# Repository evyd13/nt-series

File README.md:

# nt-series

## FC660C
Please see the controller for the FC660C [here](https://github.com/evyd13/fc660c-controller).

## About
Replacement PCBs for the FC660m, FC750r, FC980m and FC210TP.

Each of these PCBs have been tested by me, but I cannot guarantee that they work for you.

Use the latest nightly version of KiCAD to open these files. Gerbers and BOM are included for every PCB.

## Stabilizers
All of these PCB designs support PCB mounted stabilizers, but only with a custom made plate, as the stock plate tabs prevent you from putting the plate and PCB together with PCB mounted stabilizers installed.

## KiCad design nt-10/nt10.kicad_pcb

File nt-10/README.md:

# nt-10 daughterboard for Leopold keyboards

The nt-10 is a USB-C daughterboard designed to fit the Leopold range of keyboards.  
At the time of writing those are the:

- FC750r
- FC980m
- FC900r

## Installation

Upon removal of the old (probably Mini USB) daughterboard, carefully insert the nt-10 and make sure the USB-C connector fits the cutout in the case. If it does not fit, you can use a small file to increase the cutout size.

### Wiring

The wiring is as follows:

You might have to swap the wires on some boards, I had to on the 980m. Lift up the tabs using tweezers or a small knife (don't hurt yourself!) and take out the wires, then press the tabs back down and insert the wires in the correct order.

## BOM

| LCSC part # | Description   | Value | Package  | Amount |
| ----------- | ------------- | ----- | -------- | ------:|
| C27834      | Resistor      | 5.1k  | 0805     | 2      |
| C261942     | Fuse          |       | 0805     | 1      |
| C7519       | ESD prot.     |       | SOT32-6  | 1      |
| C165948     | USB-C conn.   |       |          | 1      |
| C160404     | JST SH 1x4    |       |          | 1      |
| C392176     | PicoBlade 1x5 |       |          | 1      |

Use at your own risk.

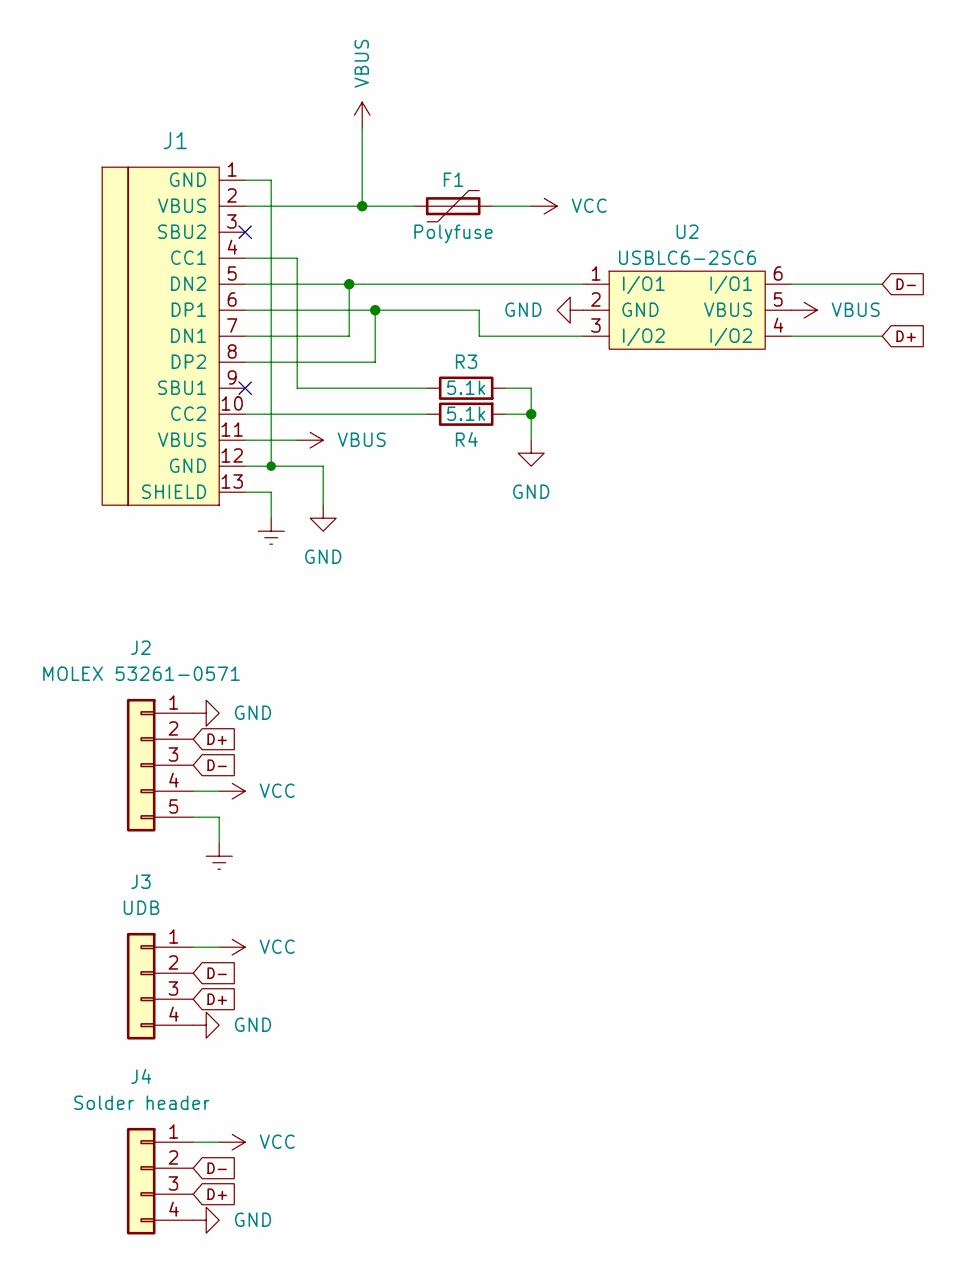
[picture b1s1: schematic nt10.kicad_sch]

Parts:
F1: Polyfuse; F_0805; LCSC Part C261942
J1: HRO-TYPE-C-31-M-12; LCSC Part C165948
J2: MOLEX 53261-0571; Molex_PicoBlade_53261-0571_1x05-1MP_P1.25mm_Horizontal; LCSC Part C392176
J3: UDB; CONN_JST_SH_SM04B-SRSS-TB_1x04-1MP_P1.00mm_Horizontal; LCSC Part C160404
J4: Solder header; 01x04-solder-header
R3, R4: 5.1k; R_0805; LCSC Part C27834
U2: USBLC6-2SC6; LCSC Part C7519

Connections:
D+: J2.2, J3.3, J4.3, U2.4 (I/O2)
D-: J2.3, J3.2, J4.2, U2.6 (I/O1)
Earth: J1.13 (SHIELD), J2.5
GND: J1.1 (GND), J1.12 (GND), J2.1, J3.4, J4.4, R3.2, R4.2, U2.2 (GND)
unnamed: J1.4 (CC1), R3.1
unnamed: J1.5 (DN2), J1.7 (DN1), U2.1 (I/O1)
unnamed: J1.6 (DP1), J1.8 (DP2), U2.3 (I/O2)
unnamed: J1.10 (CC2), R4.1
VBUS: F1.1, J1.2 (VBUS), J1.11 (VBUS), U2.5 (VBUS)
VCC: F1.2, J2.4, J3.1, J4.1

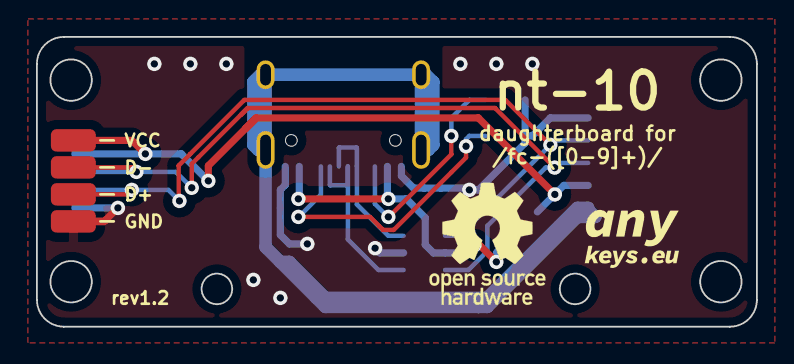
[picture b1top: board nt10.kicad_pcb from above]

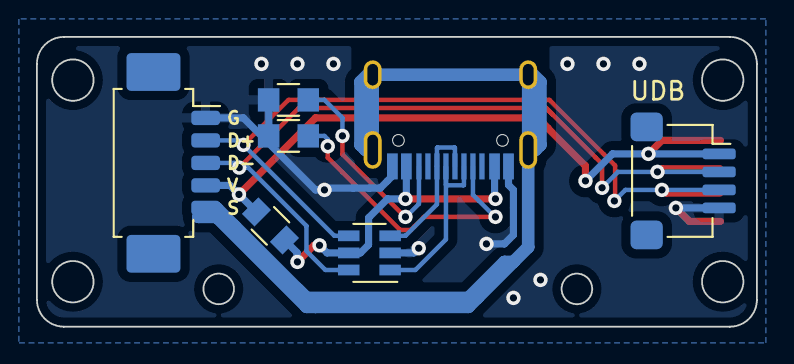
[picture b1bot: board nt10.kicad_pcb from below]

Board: 2 copper layers, 40.0 x 16.1 mm, 8 parts (7 on the bottom side), 10 nets.

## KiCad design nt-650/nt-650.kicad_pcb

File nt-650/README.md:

# nt-650

This is a replacement controller PCB for the FC650M.

## Revisions

### rev1
First revision

## BOM

| LCSC part # | Description   | Value | Package  | Amount |
| ----------- | ------------- | ----- | -------- | ------:|
| C14663      | Capacitor     | 0.1uF | 0603     | 4      |
| C19666      | Capacitor     | 4.7uF | 0603     | 1      |
| C15849      | Capacitor     | 1uF   | 0603     | 1      |
| C261942     | Fuse          |       | 0805     | 1      |
| C124360     | Pin header    | 2x16  | TH       | 1      |
| C25804      | Resistor      | 10K   | 0603     | 2      |
| C112161     | MCU           | 32U4  | QFN-44   | 1      |
| C341521     | Resonator     | 16MHz | SMD      | 1      |
| C92584      | Switch        |       | SMD      | 1      |

Use at your own risk.

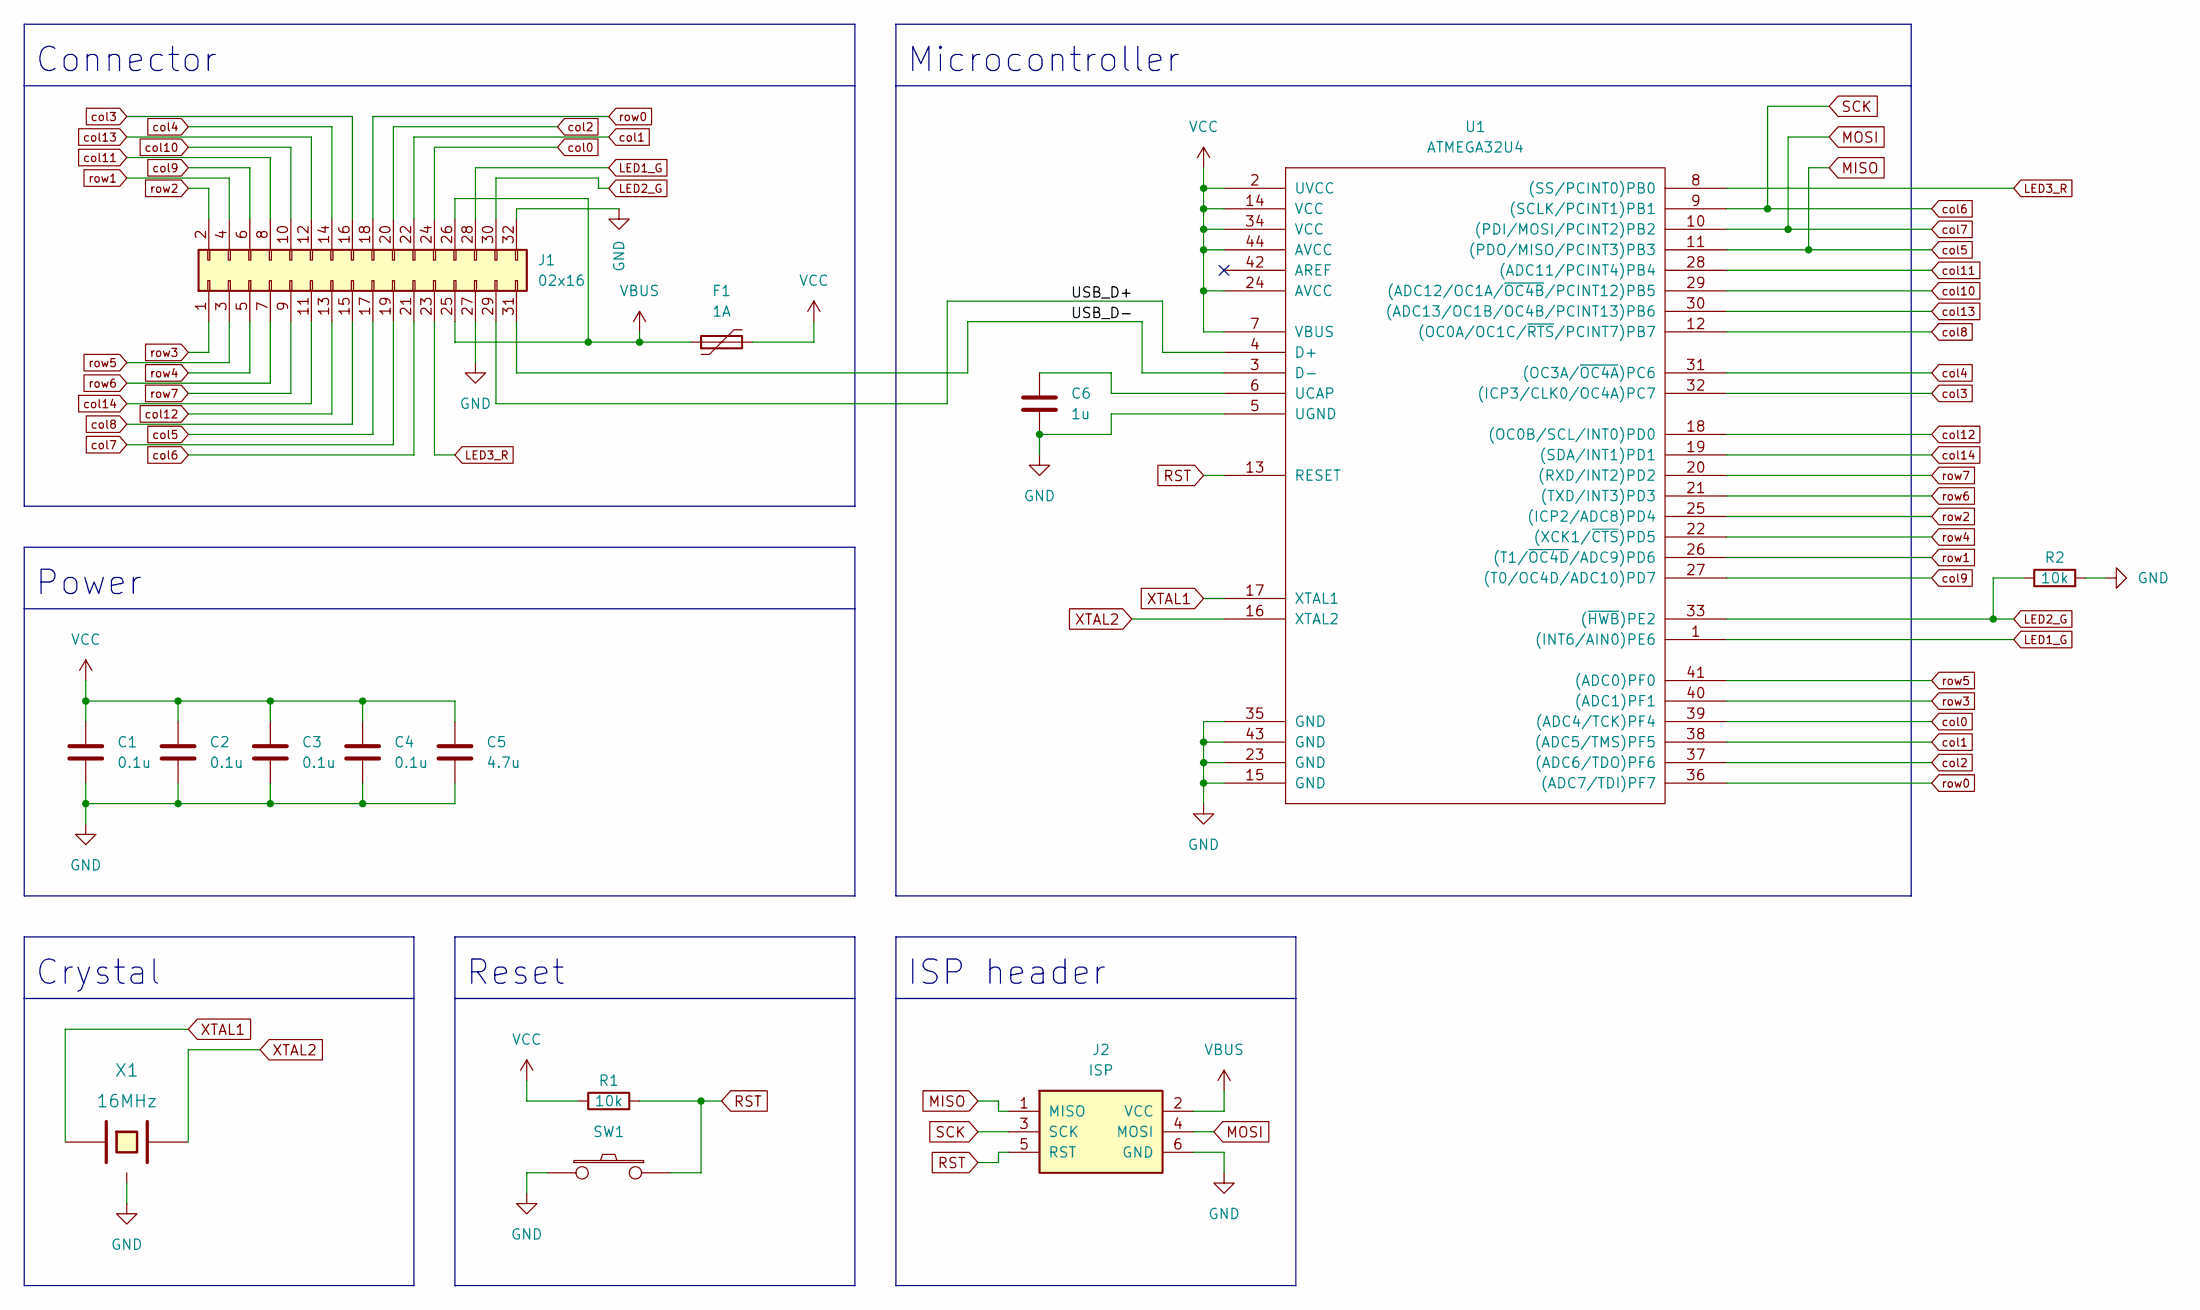
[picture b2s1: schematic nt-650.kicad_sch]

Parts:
C1, C2, C3, C4: 0.1u; C_0603; Part number CC0603KRX7R9BB104; LCSC Part C14663
C5: 4.7u; C_0603; Part number CL10A475KO8NNNC; LCSC Part C19666
C6: 1u; C_0603; Part number CL10A105KB8NNNC; LCSC Part C15849
F1: 1A; R_0805; Part number TLC-PSMD050; LCSC Part C261942
J1: 02x16; PinHeader_2x16_P2.00mm_Vertical; JLCPCB BOM 0
J2: ISP; CONN_isp_standard; JLCPCB BOM 0
R1, R2: 10k; R_0603; Part number 0603WAF1002T5E; LCSC Part C25804
SW1: SW_PUSH; SWITCH_SPST_TL3342_W_JUMP; Part number TS-1187A-B-A-B; LCSC Part C318884
U1: ATMEGA32U4; MCU_ATMEGA32U4-MU; Part number ATMEGA32U4-MU; LCSC Part C112161
X1: 16MHz; XTAL_SMD_Murata_CSTxExxV-3Pin_3.0x1.1mm; Part number CSTNE16M0V530000R0; LCSC Part C341521

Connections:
/USB_D+: J1.29, U1.4 (D+)
/USB_D-: J1.31, U1.3 (D-)
GND: C1.2, C2.2, C3.2, C4.2, C5.2, C6.2, J1.27, J1.32, J2.6 (GND), R2.2, SW1.1, U1.5 (UGND), U1.15 (GND), U1.23 (GND), U1.35 (GND), U1.43 (GND), X1.3
LED1_G: J1.28, U1.1 ((INT6/AIN0)PE6)
LED2_G: J1.30, R2.1, U1.33 ((~HWB)PE2)
LED3_R: J1.23, U1.8 ((SS/PCINT0)PB0)
MISO: J1.17, J2.1 (MISO), U1.11 ((PDO/MISO/PCINT3)PB3)
MOSI: J1.19, J2.4 (MOSI), U1.10 ((PDI/MOSI/PCINT2)PB2)
unnamed: C6.1, U1.6 (UCAP)
RST: J2.5 (RST), R1.2, SW1.2, U1.13 (RESET)
SCK: J1.21, J2.3 (SCK), U1.9 ((SCLK/PCINT1)PB1)
VBUS: F1.1, J1.25, J1.26, J2.2 (VCC)
VCC: C1.1, C2.1, C3.1, C4.1, C5.1, F1.2, R1.1, U1.2 (UVCC), U1.7 (VBUS), U1.14 (VCC), U1.24 (AVCC), U1.34 (VCC), U1.44 (AVCC)
XTAL1: U1.17 (XTAL1), X1.1
XTAL2: U1.16 (XTAL2), X1.2
col0: J1.24, U1.39 ((ADC4/TCK)PF4)
col1: J1.22, U1.38 ((ADC5/TMS)PF5)
col2: J1.20, U1.37 ((ADC6/TDO)PF6)
col3: J1.16, U1.32 ((ICP3/CLK0/OC4A)PC7)
col4: J1.14, U1.31 ((OC3A/~OC4A)PC6)
col8: J1.15, U1.12 ((OC0A/OC1C/~RTS/PCINT7)PB7)
col9: J1.6, U1.27 ((T0/OC4D/ADC10)PD7)
col10: J1.10, U1.29 ((ADC12/OC1A/~OC4B/PCINT12)PB5)
col11: J1.8, U1.28 ((ADC11/PCINT4)PB4)
col12: J1.13, U1.18 ((OC0B/SCL/INT0)PD0)
col13: J1.12, U1.30 ((ADC13/OC1B/OC4B/PCINT13)PB6)
col14: J1.11, U1.19 ((SDA/INT1)PD1)
row0: J1.18, U1.36 ((ADC7/TDI)PF7)
row1: J1.4, U1.26 ((T1/~OC4D/ADC9)PD6)
row2: J1.2, U1.25 ((ICP2/ADC8)PD4)
row3: J1.1, U1.40 ((ADC1)PF1)
row4: J1.5, U1.22 ((XCK1/~CTS)PD5)
row5: J1.3, U1.41 ((ADC0)PF0)
row6: J1.7, U1.21 ((TXD/INT3)PD3)
row7: J1.9, U1.20 ((RXD/INT2)PD2)

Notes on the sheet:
Microcontroller
Power
Reset
ISP header
Crystal
Connector

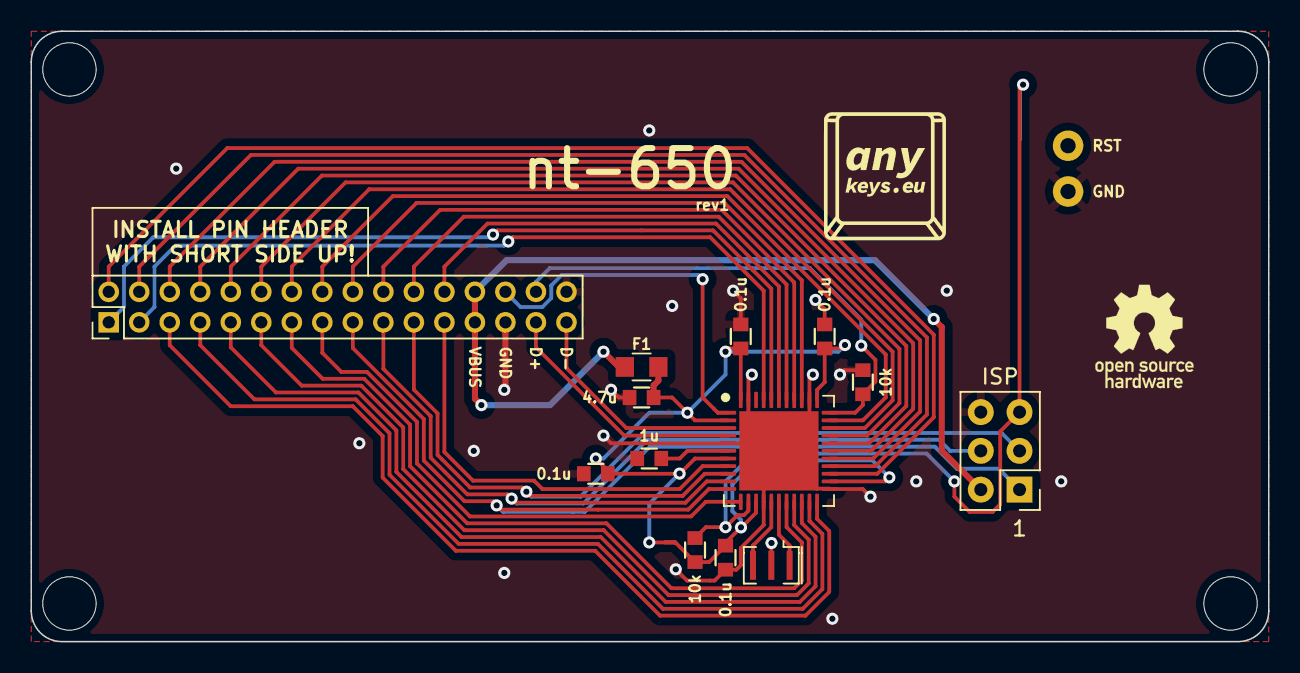
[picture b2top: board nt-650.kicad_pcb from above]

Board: 2 copper layers, 81.1 x 40.0 mm, 14 parts (1 on the bottom side), 35 nets.

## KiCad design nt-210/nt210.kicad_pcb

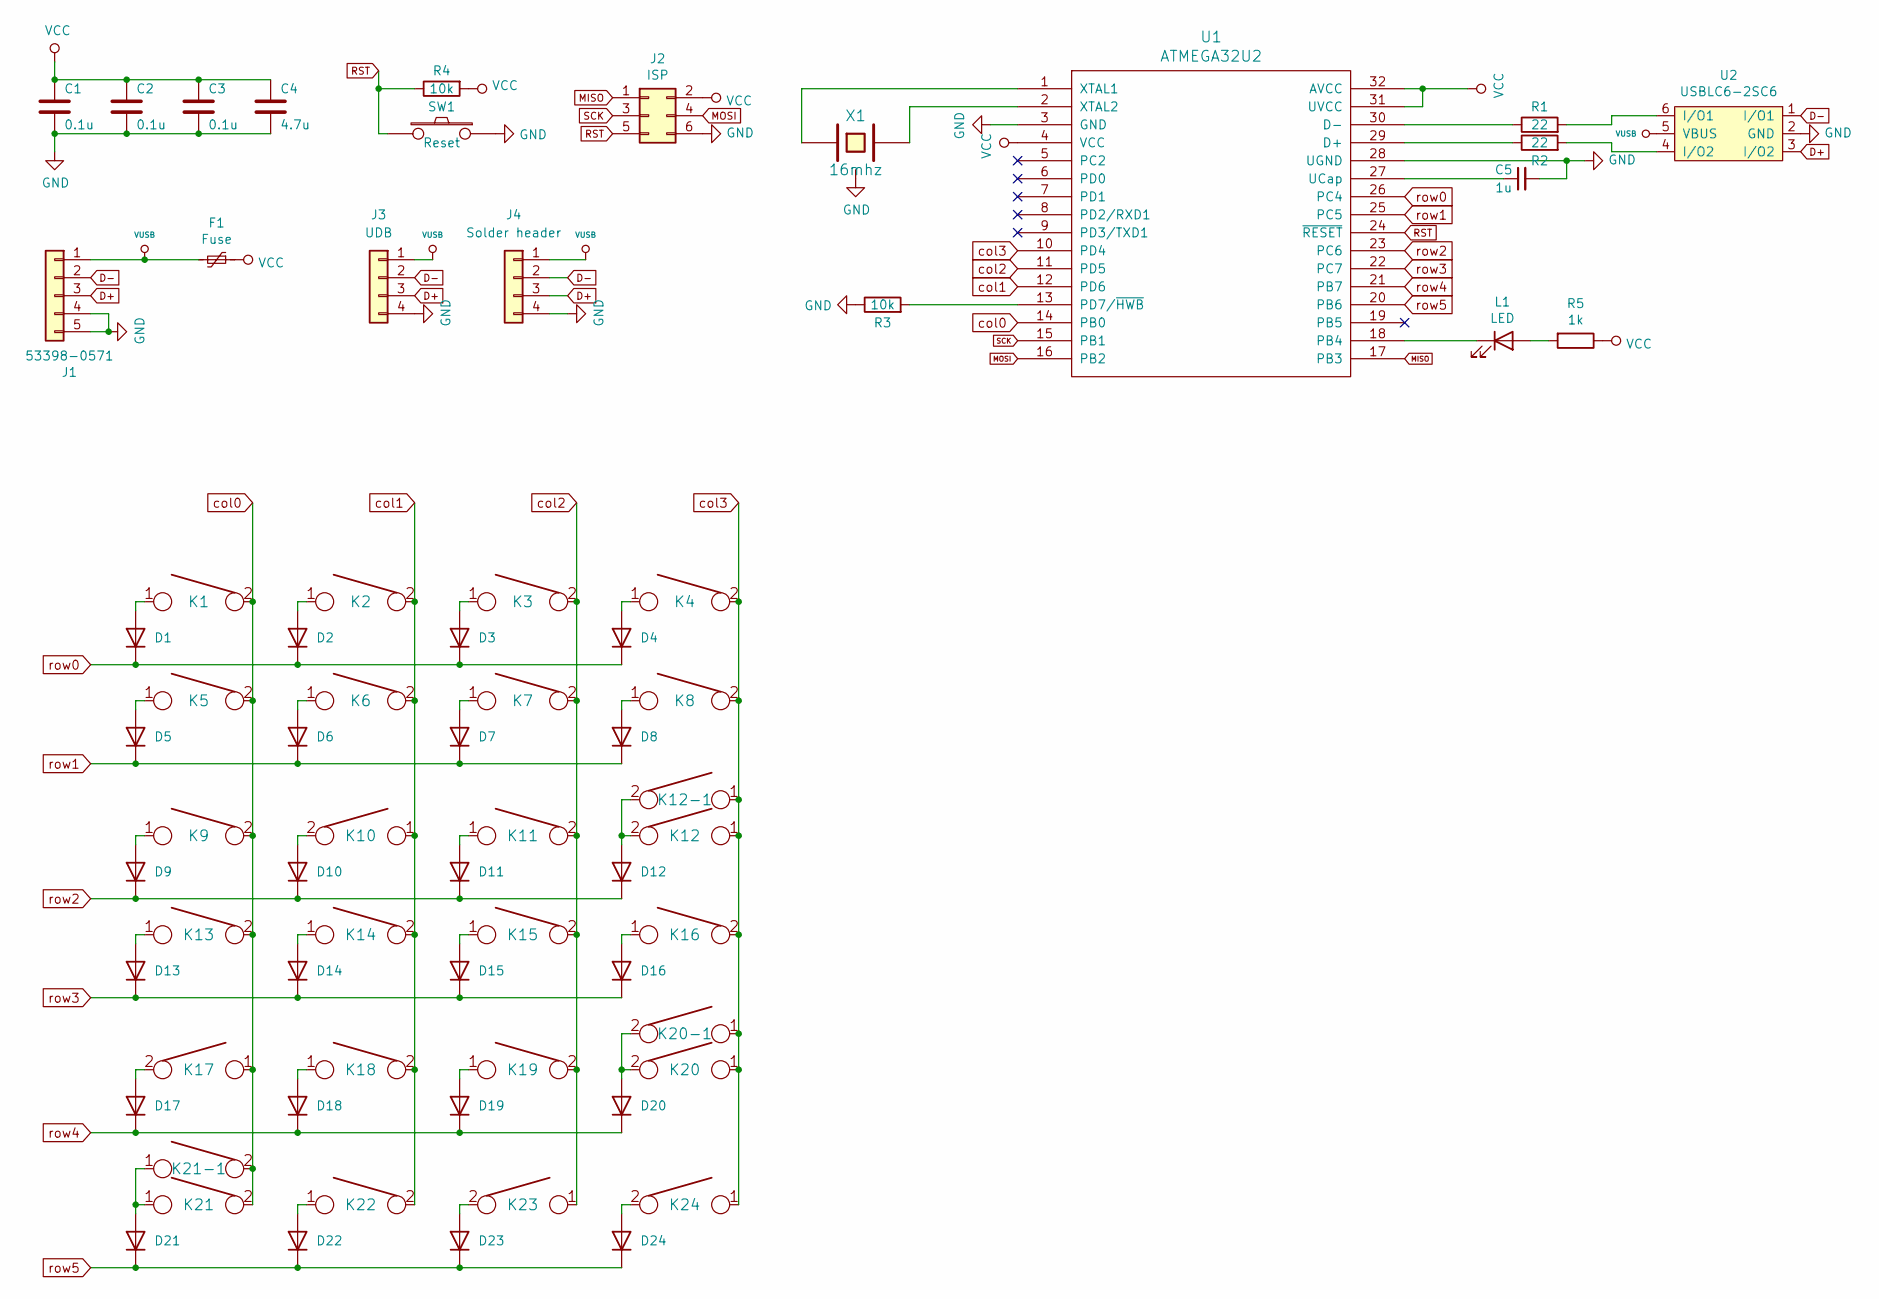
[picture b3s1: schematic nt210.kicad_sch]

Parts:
C1, C2, C3: 0.1u; C_0603
C4: 4.7u; C_0603
C5: 1u; C_0603
D1, D2, D3, D4, D5, D6, D7, D8, D9, D10, D11, D12, D13, D14, D15, D16, D17, D18, D19, D20, D21, D22, D23, D24: D; D_0805
F1: Fuse; F_0805
J1: 53398-0571; Molex-PicoBlade-533980571
J2: ISP; isp_standard
J3: UDB; JST_SH_SM04B-SRSS-TB_1x04-1MP_P1.00mm_Horizontal
J4: Solder header; solder_header
K1, K2, K3, K4, K5, K6, K7, K8, K9, K10, K11, K12-1, K13, K14, K15, K16, K17, K18, K19, K20-1, K21-1, K22, K23, K24: KEYSW; CHERRY_PLATE_100H
K12, K20: KEYSW; CHERRY_PLATE_200H_V
K21: KEYSW; CHERRY_PLATE_200H
L1: LED; CHERRY_MX_LED_neo
R1, R2: 22; R_0603
R3, R4: 10k; R_0603
R5: 1k; R_0603
SW1: Reset; SW_SPST_TL3342
U1: ATMEGA32U2
U2: USBLC6-2SC6
X1: 16mhz; Resonator_SMD_muRata_CSTNExxV-3Pin-p1.2

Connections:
D+: J1.3, J3.3, J4.3, U2.3 (I/O2)
D-: J1.2, J3.2, J4.2, U2.1 (I/O1)
GND: C1.2, C2.2, C3.2, C4.2, C5.2, J1.4, J1.5, J2.6, J3.4, J4.4, R3.1, SW1.1, U1.3 (GND), U1.28 (UGND), U2.2 (GND), X1.3
MISO: J2.1, U1.17 (PB3)
MOSI: J2.4, U1.16 (PB2)
unnamed: C5.1, U1.27 (UCap)
unnamed: D1.2 (A), K1.1
unnamed: D2.2 (A), K2.1
unnamed: D3.2 (A), K3.1
unnamed: D4.2 (A), K4.1
unnamed: D5.2 (A), K5.1
unnamed: D6.2 (A), K6.1
unnamed: D7.2 (A), K7.1
unnamed: D8.2 (A), K8.1
unnamed: D9.2 (A), K9.1
unnamed: D10.2 (A), K10.2
unnamed: D11.2 (A), K11.1
unnamed: D12.2 (A), K12.2, K12-1.2
unnamed: D13.2 (A), K13.1
unnamed: D14.2 (A), K14.1
unnamed: D15.2 (A), K15.1
unnamed: D16.2 (A), K16.1
unnamed: D17.2 (A), K17.2
unnamed: D18.2 (A), K18.1
unnamed: D19.2 (A), K19.1
unnamed: D20.2 (A), K20.2, K20-1.2
unnamed: D21.2 (A), K21.1, K21-1.1
unnamed: D22.2 (A), K22.1
unnamed: D23.2 (A), K23.2
unnamed: D24.2 (A), K24.2
unnamed: L1.1 (K), U1.18 (PB4)
unnamed: L1.2 (A), R5.2
unnamed: R1.1, U1.30 (D-)
unnamed: R1.2, U2.6 (I/O1)
unnamed: R2.1, U1.29 (D+)
unnamed: R2.2, U2.4 (I/O2)
unnamed: R3.2, U1.13 (PD7/~HWB)
unnamed: U1.1 (XTAL1), X1.1
unnamed: U1.2 (XTAL2), X1.2
RST: J2.5, R4.1, SW1.2, U1.24 (~RESET)
SCK: J2.3, U1.15 (PB1)
VCC: C1.1, C2.1, C3.1, C4.1, F1.1, J2.2, R4.2, R5.1, U1.4 (VCC), U1.31 (UVCC), U1.32 (AVCC)
VUSB: F1.2, J1.1, J3.1, J4.1, U2.5 (VBUS)
col0: K1.2, K5.2, K9.2, K13.2, K17.1, K21.2, K21-1.2, U1.14 (PB0)
col1: K2.2, K6.2, K10.1, K14.2, K18.2, K22.2, U1.12 (PD6)
col2: K3.2, K7.2, K11.2, K15.2, K19.2, K23.1, U1.11 (PD5)
col3: K4.2, K8.2, K12.1, K12-1.1, K16.2, K20.1, K20-1.1, K24.1, U1.10 (PD4)
row0: D1.1 (K), D2.1 (K), D3.1 (K), D4.1 (K), U1.26 (PC4)
row1: D5.1 (K), D6.1 (K), D7.1 (K), D8.1 (K), U1.25 (PC5)
row2: D9.1 (K), D10.1 (K), D11.1 (K), D12.1 (K), U1.23 (PC6)
row3: D13.1 (K), D14.1 (K), D15.1 (K), D16.1 (K), U1.22 (PC7)
row4: D17.1 (K), D18.1 (K), D19.1 (K), D20.1 (K), U1.21 (PB7)
row5: D21.1 (K), D22.1 (K), D23.1 (K), D24.1 (K), U1.20 (PB6)

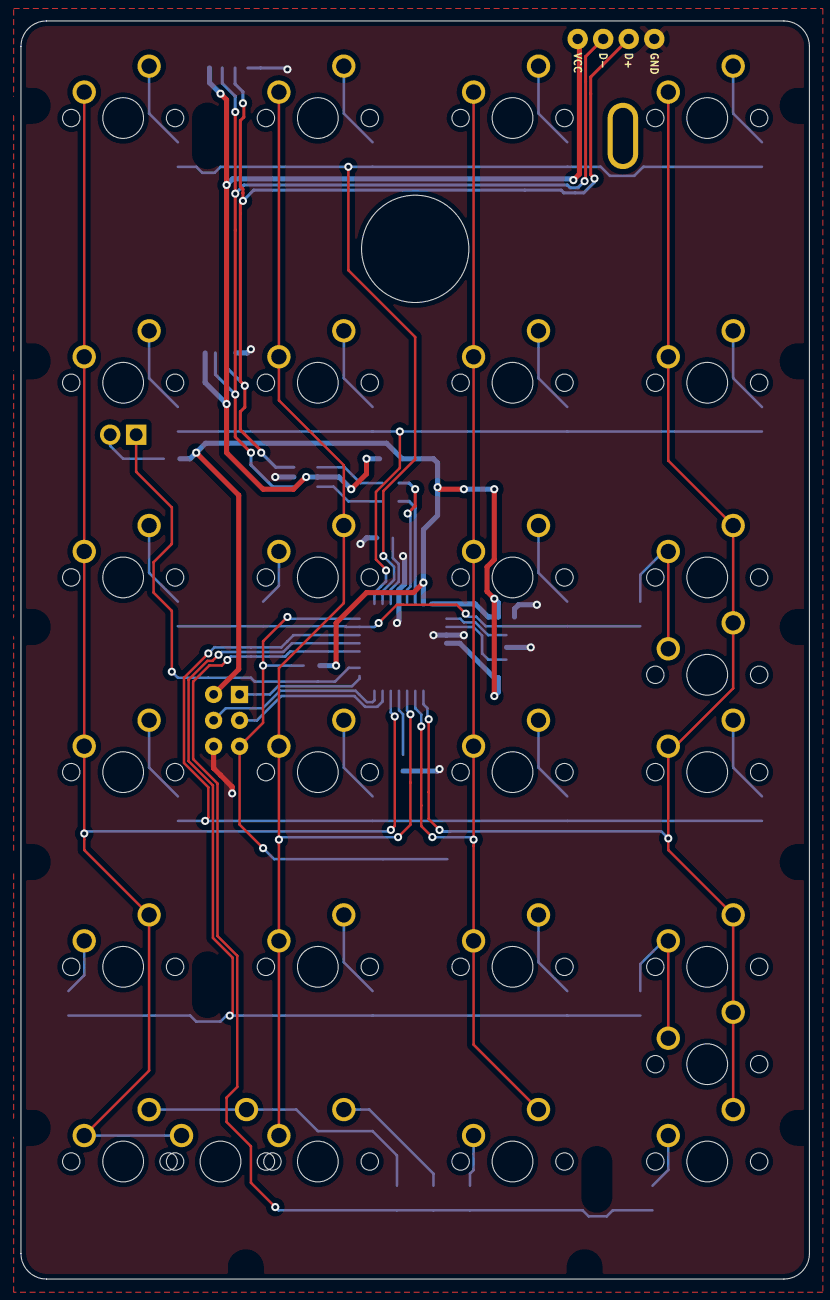
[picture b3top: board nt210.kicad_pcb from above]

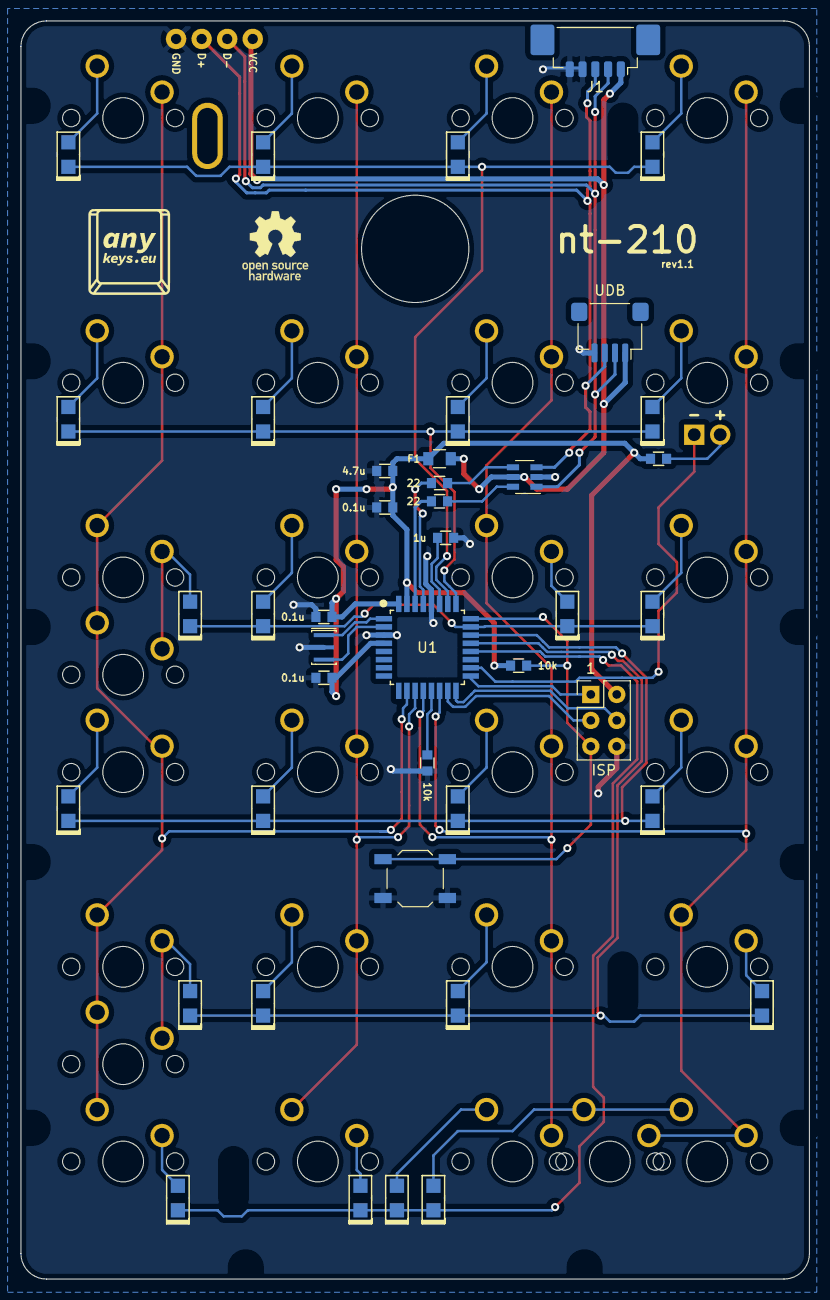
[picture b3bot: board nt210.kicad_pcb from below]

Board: 2 copper layers, 77.2 x 123.1 mm, 71 parts (42 on the bottom side), 53 nets.

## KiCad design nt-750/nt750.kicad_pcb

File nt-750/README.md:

# nt-750

This is a replacement PCB for the FC750r.

## BOM

| LCSC part # | Description   | Value | Package  | Amount |
| ----------- | ------------- | ----- | -------- | ------:|
| C128353     | Capacitor     | 0.1uF | 0805     | 4      |
| C131056     | Capacitor     | 4.7uF | 0805     | 1      |
| C215803     | Capacitor     | 1uF   | 0805     | 1      |
| C109001     | Diode         |       | 0805     | 89     |
| C261942     | Fuse          |       | 0805     | 1      |
| C157923     | Connector     |       | TH       | 1      |
| C103904     | Resistor      | 10K   | 0805     | 2      |
| C384174     | Resistor      | 1K    | 0805     | 1      |
| C325772     | Resistor      | 22    | 0805     | 2      |
| C44854      | MCU           | 32U4  | QFP-44   | 1      |
| C341521     | Resonator     | 16MHz | SMD      | 1      |
| C7519       | ESD prot.     |       | SOT23-6  | 1      |
| C92584      | Switch        |       | SMD      | 1      |

Use at your own risk.

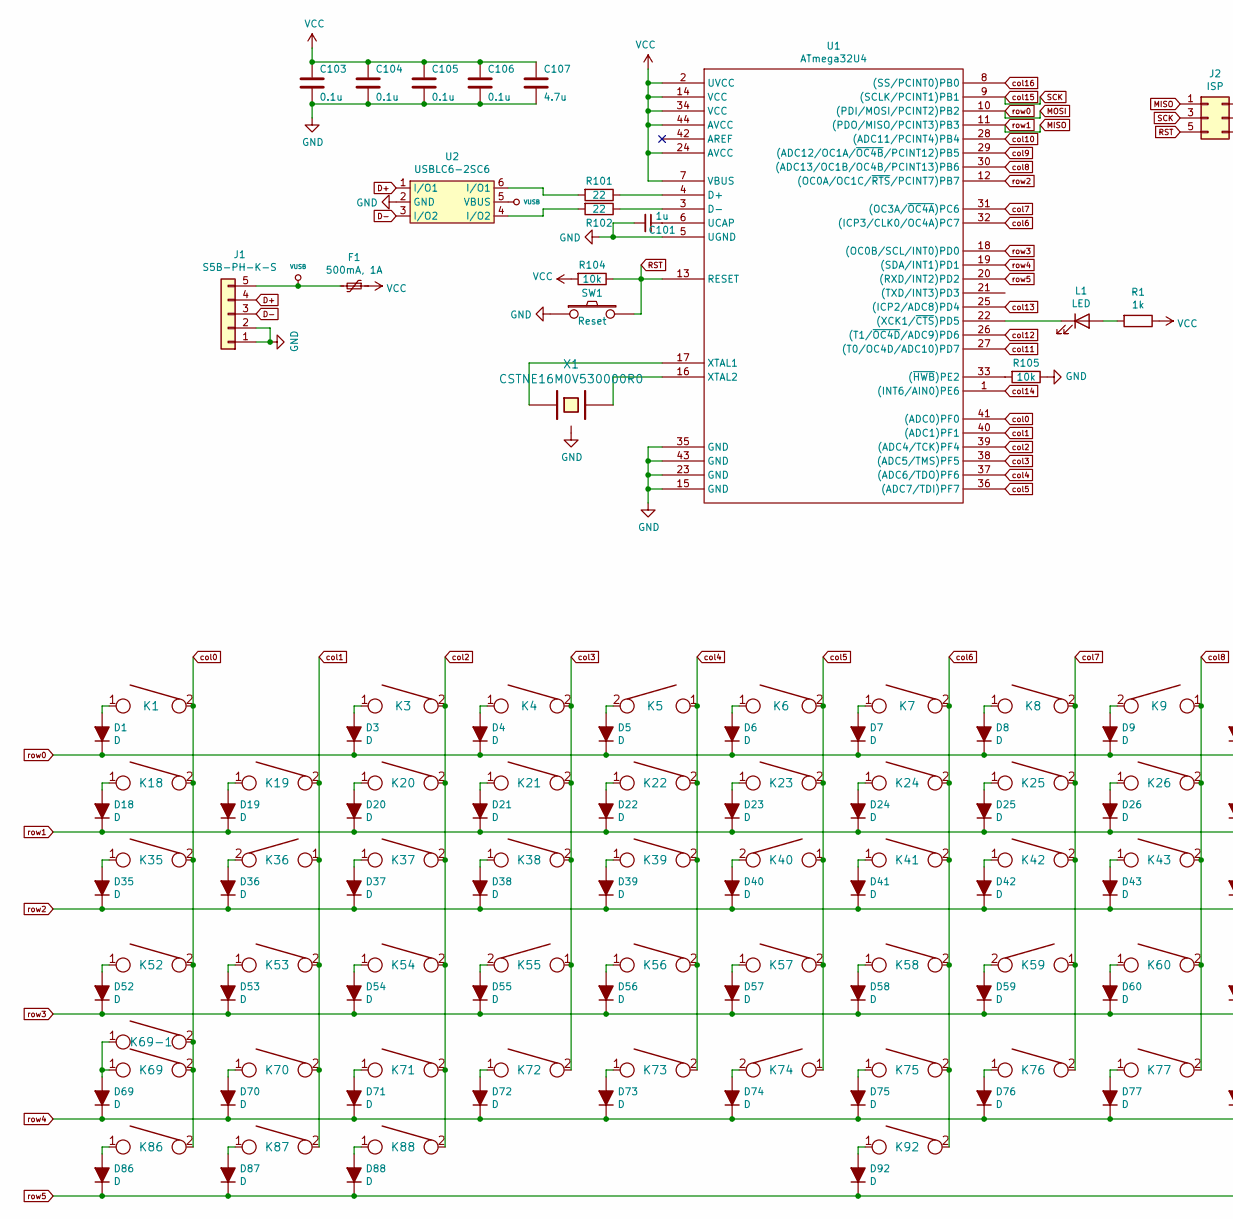
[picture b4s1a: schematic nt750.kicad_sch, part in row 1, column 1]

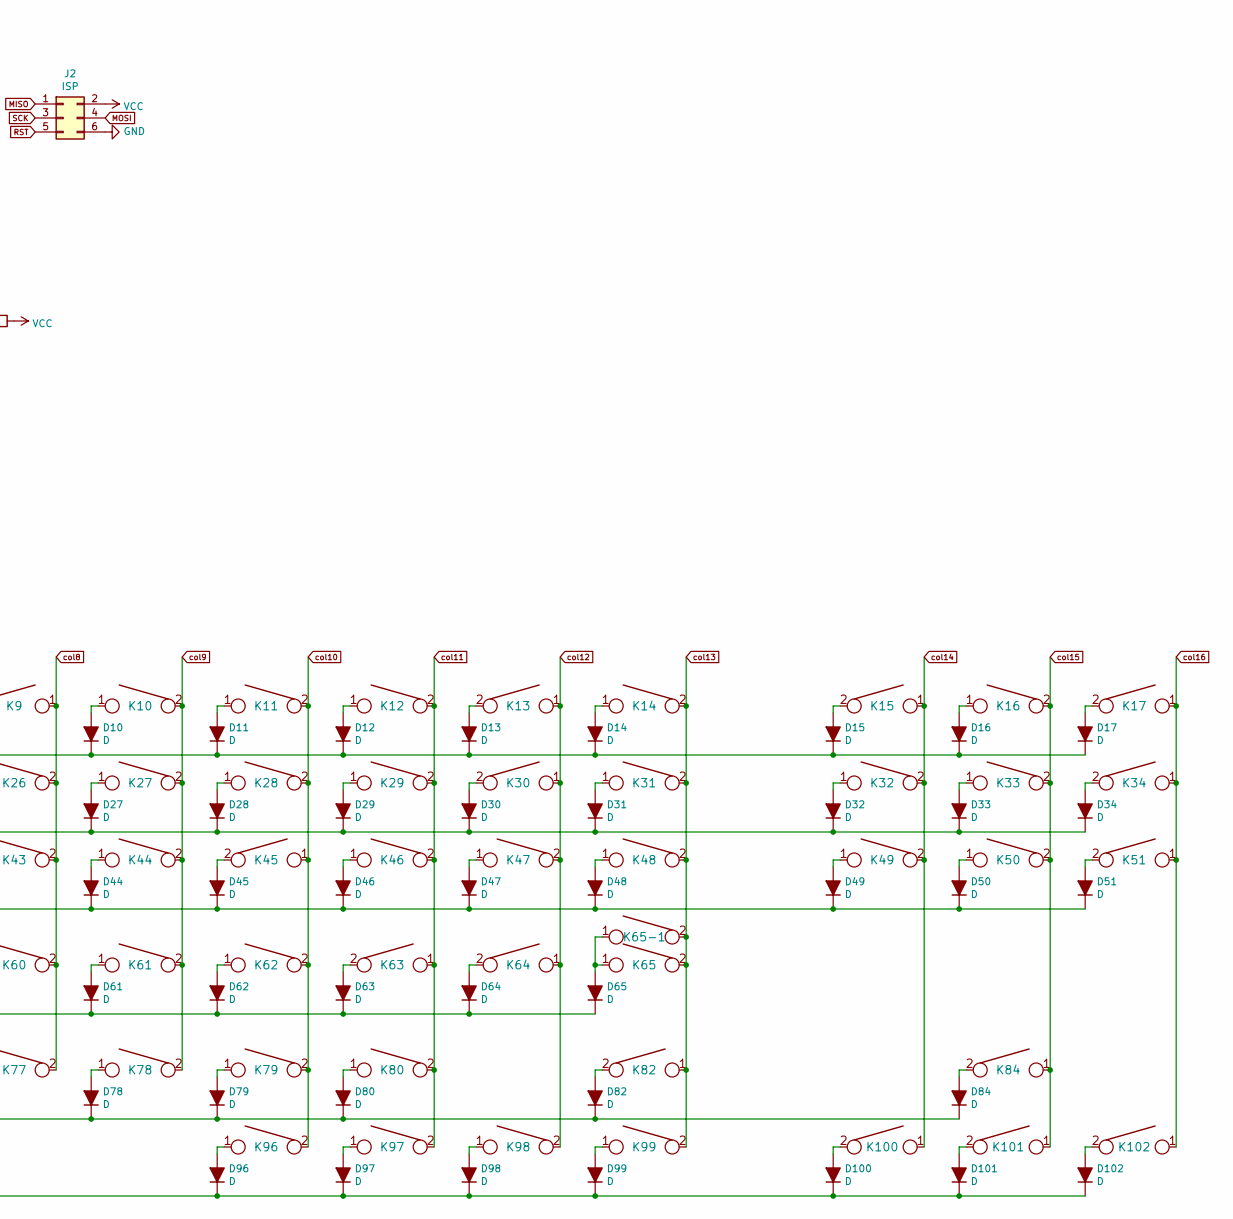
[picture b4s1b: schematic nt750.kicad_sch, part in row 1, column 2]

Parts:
C101: 1u; C_0805
C103, C104, C105, C106: 0.1u; C_0805
C107: 4.7u; C_0805
D1, D3, D4, D5, D6, D7, D8, D9, D10, D11, D12, D13, D14, D15, D16, D17, D18, D19, D20, D21, D22, D23, D24, D25, D26, D27, D28, D29, D30, D31, D32, D33, D34, D35, D36, D37, D38, D39, D40, D41, D42, D43, D44, D45, D46, D47, D48, D49, D50, D51, D52, D53, D54, D55, D56, D57, D58, D59, D60, D61, D62, D63, D64, D65, D69, D70, D71, D72, D73, D74, D75, D76, D77, D78, D79, D80, D82, D84, D86, D87, D88, D92, D96, D97, D98, D99, D100, D101, D102: D; D_0805
F1: 500mA, 1A; R_0805
J1: S5B-PH-K-S; JST_PH_S5B-PH-K_1x05_P2.00mm_Horizontal
J2: ISP; isp_standard
K1, K3, K4, K5, K6, K7, K8, K9, K10, K11, K12, K13, K14, K15, K16, K17, K18, K19, K20, K21, K22, K23, K24, K25, K26, K27, K28, K29, K30, K32, K33, K34, K36, K37, K38, K39, K40, K41, K42, K43, K44, K45, K46, K47, K49, K50, K51, K53, K54, K55, K56, K57, K58, K59, K60, K61, K62, K63, K64, K70, K71, K72, K73, K74, K75, K76, K77, K78, K79, K80, K84, K100, K101, K102: KEYSW; CHERRY_PLATE_100H
K31: KEYSW; CHERRY_PCB_200H
K35, K48: KEYSW; CHERRY_PLATE_150H
K52: KEYSW; CHERRY_PLATE_175H
K65, K69: KEYSW; CHERRY_PCB_225H
K65-1: KEYSW; CHERRY_PCB_200H_V
K69-1, K86, K87, K88, K96, K97, K98, K99: KEYSW; CHERRY_PLATE_125H
K82: KEYSW; CHERRY_PCB_275H
K92: KEYSW; CHERRY_PCB_625H_F
L1: LED; CHERRY_MX_LED
R1: 1k; R_0805
R101, R102: 22; R_0805
R104, R105: 10k; R_0805
SW1: Reset; SW_SPST_TL3342
U1: ATmega32U4; ATMEGA32U4
U2: USBLC6-2SC6
X1: CSTNE16M0V530000R0; Resonator_SMD_muRata_CSTNExxV-3Pin-p1.2

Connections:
D+: J1.4, U2.1 (I/O1)
D-: J1.3, U2.3 (I/O2)
GND: C101.2, C103.2, C104.2, C105.2, C106.2, C107.2, J1.1, J1.2, J2.6, R105.1, SW1.1, U1.5 (UGND), U1.15 (GND), U1.23 (GND), U1.35 (GND), U1.43 (GND), U2.2 (GND), X1.3
MISO: D18.1 (K), D19.1 (K), D20.1 (K), D21.1 (K), D22.1 (K), D23.1 (K), D24.1 (K), D25.1 (K), D26.1 (K), D27.1 (K), D28.1 (K), D29.1 (K), D30.1 (K), D31.1 (K), D32.1 (K), D33.1 (K), D34.1 (K), J2.1, U1.11 ((PDO/MISO/PCINT3)PB3)
MOSI: D1.1 (K), D3.1 (K), D4.1 (K), D5.1 (K), D6.1 (K), D7.1 (K), D8.1 (K), D9.1 (K), D10.1 (K), D11.1 (K), D12.1 (K), D13.1 (K), D14.1 (K), D15.1 (K), D16.1 (K), D17.1 (K), J2.4, U1.10 ((PDI/MOSI/PCINT2)PB2)
unnamed: C101.1, U1.6 (UCAP)
unnamed: D1.2 (A), K1.1
unnamed: D3.2 (A), K3.1
unnamed: D4.2 (A), K4.1
unnamed: D5.2 (A), K5.2
unnamed: D6.2 (A), K6.1
unnamed: D7.2 (A), K7.1
unnamed: D8.2 (A), K8.1
unnamed: D9.2 (A), K9.2
unnamed: D10.2 (A), K10.1
unnamed: D11.2 (A), K11.1
unnamed: D12.2 (A), K12.1
unnamed: D13.2 (A), K13.2
unnamed: D14.2 (A), K14.1
unnamed: D15.2 (A), K15.2
unnamed: D16.2 (A), K16.1
unnamed: D17.2 (A), K17.2
unnamed: D18.2 (A), K18.1
unnamed: D19.2 (A), K19.1
unnamed: D20.2 (A), K20.1
unnamed: D21.2 (A), K21.1
unnamed: D22.2 (A), K22.1
unnamed: D23.2 (A), K23.1
unnamed: D24.2 (A), K24.1
unnamed: D25.2 (A), K25.1
unnamed: D26.2 (A), K26.1
unnamed: D27.2 (A), K27.1
unnamed: D28.2 (A), K28.1
unnamed: D29.2 (A), K29.1
unnamed: D30.2 (A), K30.2
unnamed: D31.2 (A), K31.1
unnamed: D32.2 (A), K32.1
unnamed: D33.2 (A), K33.1
unnamed: D34.2 (A), K34.2
unnamed: D35.2 (A), K35.1
unnamed: D36.2 (A), K36.2
unnamed: D37.2 (A), K37.1
unnamed: D38.2 (A), K38.1
unnamed: D39.2 (A), K39.1
unnamed: D40.2 (A), K40.2
unnamed: D41.2 (A), K41.1
unnamed: D42.2 (A), K42.1
unnamed: D43.2 (A), K43.1
unnamed: D44.2 (A), K44.1
unnamed: D45.2 (A), K45.2
unnamed: D46.2 (A), K46.1
unnamed: D47.2 (A), K47.1
unnamed: D48.2 (A), K48.1
unnamed: D49.2 (A), K49.1
unnamed: D50.2 (A), K50.1
unnamed: D51.2 (A), K51.2
unnamed: D52.2 (A), K52.1
unnamed: D53.2 (A), K53.1
unnamed: D54.2 (A), K54.1
unnamed: D55.2 (A), K55.2
unnamed: D56.2 (A), K56.1
unnamed: D57.2 (A), K57.1
unnamed: D58.2 (A), K58.1
unnamed: D59.2 (A), K59.2
unnamed: D60.2 (A), K60.1
unnamed: D61.2 (A), K61.1
unnamed: D62.2 (A), K62.1
unnamed: D63.2 (A), K63.2
unnamed: D64.2 (A), K64.2
unnamed: D65.2 (A), K65.1, K65-1.1
unnamed: D69.2 (A), K69.1, K69-1.1
unnamed: D70.2 (A), K70.1
unnamed: D71.2 (A), K71.1
unnamed: D72.2 (A), K72.1
unnamed: D73.2 (A), K73.1
unnamed: D74.2 (A), K74.2
unnamed: D75.2 (A), K75.1
unnamed: D76.2 (A), K76.1
unnamed: D77.2 (A), K77.1
unnamed: D78.2 (A), K78.1
unnamed: D79.2 (A), K79.1
unnamed: D80.2 (A), K80.1
unnamed: D82.2 (A), K82.2
unnamed: D84.2 (A), K84.2
unnamed: D86.2 (A), K86.1
unnamed: D87.2 (A), K87.1
unnamed: D88.2 (A), K88.1
unnamed: D92.2 (A), K92.1
unnamed: D96.2 (A), K96.1
unnamed: D97.2 (A), K97.1
unnamed: D98.2 (A), K98.1
unnamed: D99.2 (A), K99.1
unnamed: D100.2 (A), K100.2
unnamed: D101.2 (A), K101.2
unnamed: D102.2 (A), K102.2
unnamed: L1.1 (K), U1.22 ((XCK1/~CTS~)PD5)
unnamed: L1.2 (A), R1.2
unnamed: R101.1, U1.4 (D+)
unnamed: R101.2, U2.6 (I/O1)
unnamed: R102.1, U1.3 (D-)
unnamed: R102.2, U2.4 (I/O2)
unnamed: R105.2, U1.33 ((~HWB~)PE2)
unnamed: U1.16 (XTAL2), X1.2
unnamed: U1.17 (XTAL1), X1.1
RST: J2.5, R104.1, SW1.2, U1.13 (RESET)
SCK: J2.3, K16.2, K33.2, K50.2, K84.1, K101.1, U1.9 ((SCLK/PCINT1)PB1)
VCC: C103.1, C104.1, C105.1, C106.1, C107.1, F1.1, J2.2, R1.1, R104.2, U1.2 (UVCC), U1.7 (VBUS), U1.14 (VCC), U1.24 (AVCC), U1.34 (VCC), U1.44 (AVCC)
VUSB: F1.2, J1.5, U2.5 (VBUS)
col0: K1.2, K18.2, K35.2, K52.2, K69.2, K69-1.2, K86.2, U1.41 ((ADC0)PF0)
col1: K19.2, K36.1, K53.2, K70.2, K87.2, U1.40 ((ADC1)PF1)
col2: K3.2, K20.2, K37.2, K54.2, K71.2, K88.2, U1.39 ((ADC4/TCK)PF4)
col3: K4.2, K21.2, K38.2, K55.1, K72.2, U1.38 ((ADC5/TMS)PF5)
col4: K5.1, K22.2, K39.2, K56.2, K73.2, U1.37 ((ADC6/TDO)PF6)
col5: K6.2, K23.2, K40.1, K57.2, K74.1, U1.36 ((ADC7/TDI)PF7)
col6: K7.2, K24.2, K41.2, K58.2, K75.2, K92.2, U1.32 ((ICP3/CLK0/OC4A)PC7)
col7: K8.2, K25.2, K42.2, K59.1, K76.2, U1.31 ((OC3A/~OC4A~)PC6)
col8: K9.1, K26.2, K43.2, K60.2, K77.2, U1.30 ((ADC13/OC1B/OC4B/PCINT13)PB6)
col9: K10.2, K27.2, K44.2, K61.2, K78.2, U1.29 ((ADC12/OC1A/~OC4B~/PCINT12)PB5)
col10: K11.2, K28.2, K45.1, K62.2, K79.2, K96.2, U1.28 ((ADC11/PCINT4)PB4)
col11: K12.2, K29.2, K46.2, K63.1, K80.2, K97.2, U1.27 ((T0/OC4D/ADC10)PD7)
col12: K13.1, K30.1, K47.2, K64.1, K98.2, U1.26 ((T1/~OC4D~/ADC9)PD6)
col13: K14.2, K31.2, K48.2, K65.2, K65-1.2, K82.1, K99.2, U1.25 ((ICP2/ADC8)PD4)
col14: K15.1, K32.2, K49.2, K100.1, U1.1 ((INT6/AIN0)PE6)
col16: K17.1, K34.1, K51.1, K102.1, U1.8 ((SS/PCINT0)PB0)
row2: D35.1 (K), D36.1 (K), D37.1 (K), D38.1 (K), D39.1 (K), D40.1 (K), D41.1 (K), D42.1 (K), D43.1 (K), D44.1 (K), D45.1 (K), D46.1 (K), D47.1 (K), D48.1 (K), D49.1 (K), D50.1 (K), D51.1 (K), U1.12 ((OC0A/OC1C/~RTS~/PCINT7)PB7)
row3: D52.1 (K), D53.1 (K), D54.1 (K), D55.1 (K), D56.1 (K), D57.1 (K), D58.1 (K), D59.1 (K), D60.1 (K), D61.1 (K), D62.1 (K), D63.1 (K), D64.1 (K), D65.1 (K), U1.18 ((OC0B/SCL/INT0)PD0)
row4: D69.1 (K), D70.1 (K), D71.1 (K), D72.1 (K), D73.1 (K), D74.1 (K), D75.1 (K), D76.1 (K), D77.1 (K), D78.1 (K), D79.1 (K), D80.1 (K), D82.1 (K), D84.1 (K), U1.19 ((SDA/INT1)PD1)
row5: D86.1 (K), D87.1 (K), D88.1 (K), D92.1 (K), D96.1 (K), D97.1 (K), D98.1 (K), D99.1 (K), D100.1 (K), D101.1 (K), D102.1 (K), U1.20 ((RXD/INT2)PD2)
